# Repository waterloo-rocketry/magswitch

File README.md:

# magswitch
Repo for the design of an SRAD mag switch.

Design doc here: https://docs.google.com/document/d/1IFNrE6rn7PapjevV3imXdUjNrR9YV5aXWS5f5mARtcY/edit?usp=sharing

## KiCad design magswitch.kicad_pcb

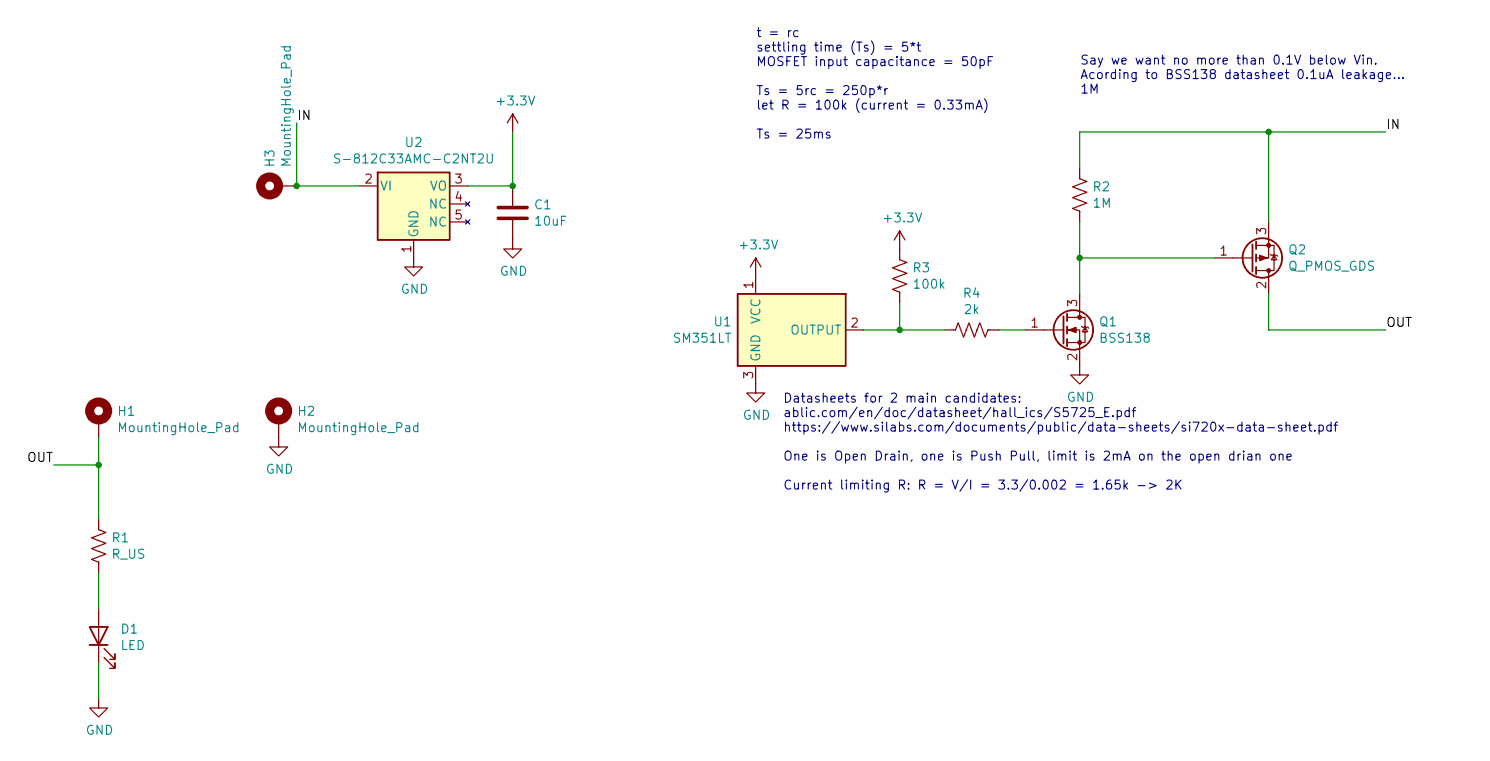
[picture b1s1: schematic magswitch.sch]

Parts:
C1: 10uF; C_0805_2012Metric
D1: LED; LED_0603_1608Metric_Pad1.05x0.95mm_HandSolder
H1, H2, H3: MountingHole_Pad; MountingHole_3.2mm_M3_Pad_Via
Q1: BSS138; SOT-23
Q2: Q_PMOS_GDS; SOIC-8_MOSFET
R1: R_US; R_0603_1608Metric
R2: 1M; R_0603_1608Metric_Pad1.05x0.95mm_HandSolder
R3: 100k; R_0603_1608Metric_Pad1.05x0.95mm_HandSolder
R4: 2k; R_0603_1608Metric_Pad1.05x0.95mm_HandSolder
U1: SM351LT; SOT-23
U2: S-812C33AMC-C2NT2U; SOT-23-5

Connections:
+3V3: C1.1, R3.1, U1.1 (VCC), U2.3 (VO)
/IN: H3.1, Q2.3 (S), R2.1, U2.2 (VI)
/OUT: H1.1, Q2.2 (D), R1.1
GND: C1.2, D1.1 (K), H2.1, Q1.2 (S), U1.3 (GND), U2.1 (GND)
unnamed: D1.2 (A), R1.2
unnamed: Q1.1 (G), R4.1
unnamed: Q1.3 (D), Q2.1 (G), R2.2
unnamed: R3.2, R4.2, U1.2 (OUTPUT)

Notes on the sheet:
Datasheets for 2 main candidates: ablic.com/en/doc/datasheet/hall_ics/S5725_E.pdf https://www.silabs.com/documents/public/data-sheets/si720x-data-sheet.pdf One is Open Drain, one is Push Pull, limit is 2mA on the open drian one Current limiting R: R = V/I = 3.3/0.002 = 1.65k -> 2K
Say we want no more than 0.1V below Vin. Acording to BSS138 datasheet 0.1uA leakage... 1M
t = rc settling time (Ts) = 5*t MOSFET input capacitance = 50pF Ts = 5rc = 250p*r let R = 100k (current = 0.33mA) Ts = 25ms

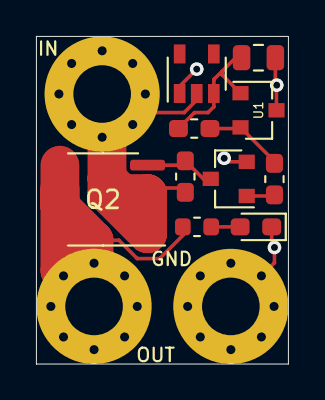
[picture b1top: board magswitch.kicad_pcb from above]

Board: 2 copper layers, 14.0 x 18.2 mm, 13 parts (0 on the bottom side), 8 nets.

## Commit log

2021-04-03 Create kicad project and gitignore
2021-04-10 Create initial magswitch schematic and layout
2021-04-10 Complete board tracing.
2021-05-01 Add pdf
2021-05-11 Address Chamath's comments and add gerbers
2021-05-15 Add LED resistor value.
